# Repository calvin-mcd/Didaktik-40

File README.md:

# Didaktik 40

The Didaktik 40 is a retro-style keyboard taking its inspiration form the czech homecomputer, the [didaktik gama](https://en.wikipedia.org/wiki/Didaktik#Didaktik_Gama). While offering its original layout, it also supports more modern split and single spacebar bottomrow configurations as well as two rotary encoders.
The case is designed by gizzle13. It is a 2 degree, 2 piece case with top mounting for either simple or burger topmounting. It uses an old-school unified daughterboard for the usb port. The case and pcb furthermore support 2 leds, just like on the original case, and another hole to access the reset button.

## Layout

[Link](http://www.keyboard-layout-editor.com/#/gists/80f2dfd555ef09043852ad12f22f6b8f)

## Firmware

The basic firmware is set up to use the leds as layer indicators. Top for layer 1, bottom for layer 2, both for layer 3. There is hardware support for a speaker and for rgb strip but this is not enabled by default due to firmware size. Also note that the audio and rgb haven't been fully tested yet.

## Case

The case is designed by gizzle13. Case files can be found in the respective folder. It is designed to use m2 heatinserts. 

If you are in the EU consider asking gizzle to print the case for you to support them!

## Disclaimer

This PCB has been fully tested and confirmed to work. The members of the PCB development team are however not liable if you end up with a non-functional pcb. Order at your own risk. Support will not be provided but pull requests will be reviewed and possibly accepted.

## License

This project is released under the GPL v3 License. Please refer to the LICENCE file.

## Credits

big thanks to gizzle13 for making this project possible. The whole idea really lives and thrives with the case!

As always big thanks also to the many people who inspired and helped with this board!

Any questions, contact Calvin0563 on Discord.

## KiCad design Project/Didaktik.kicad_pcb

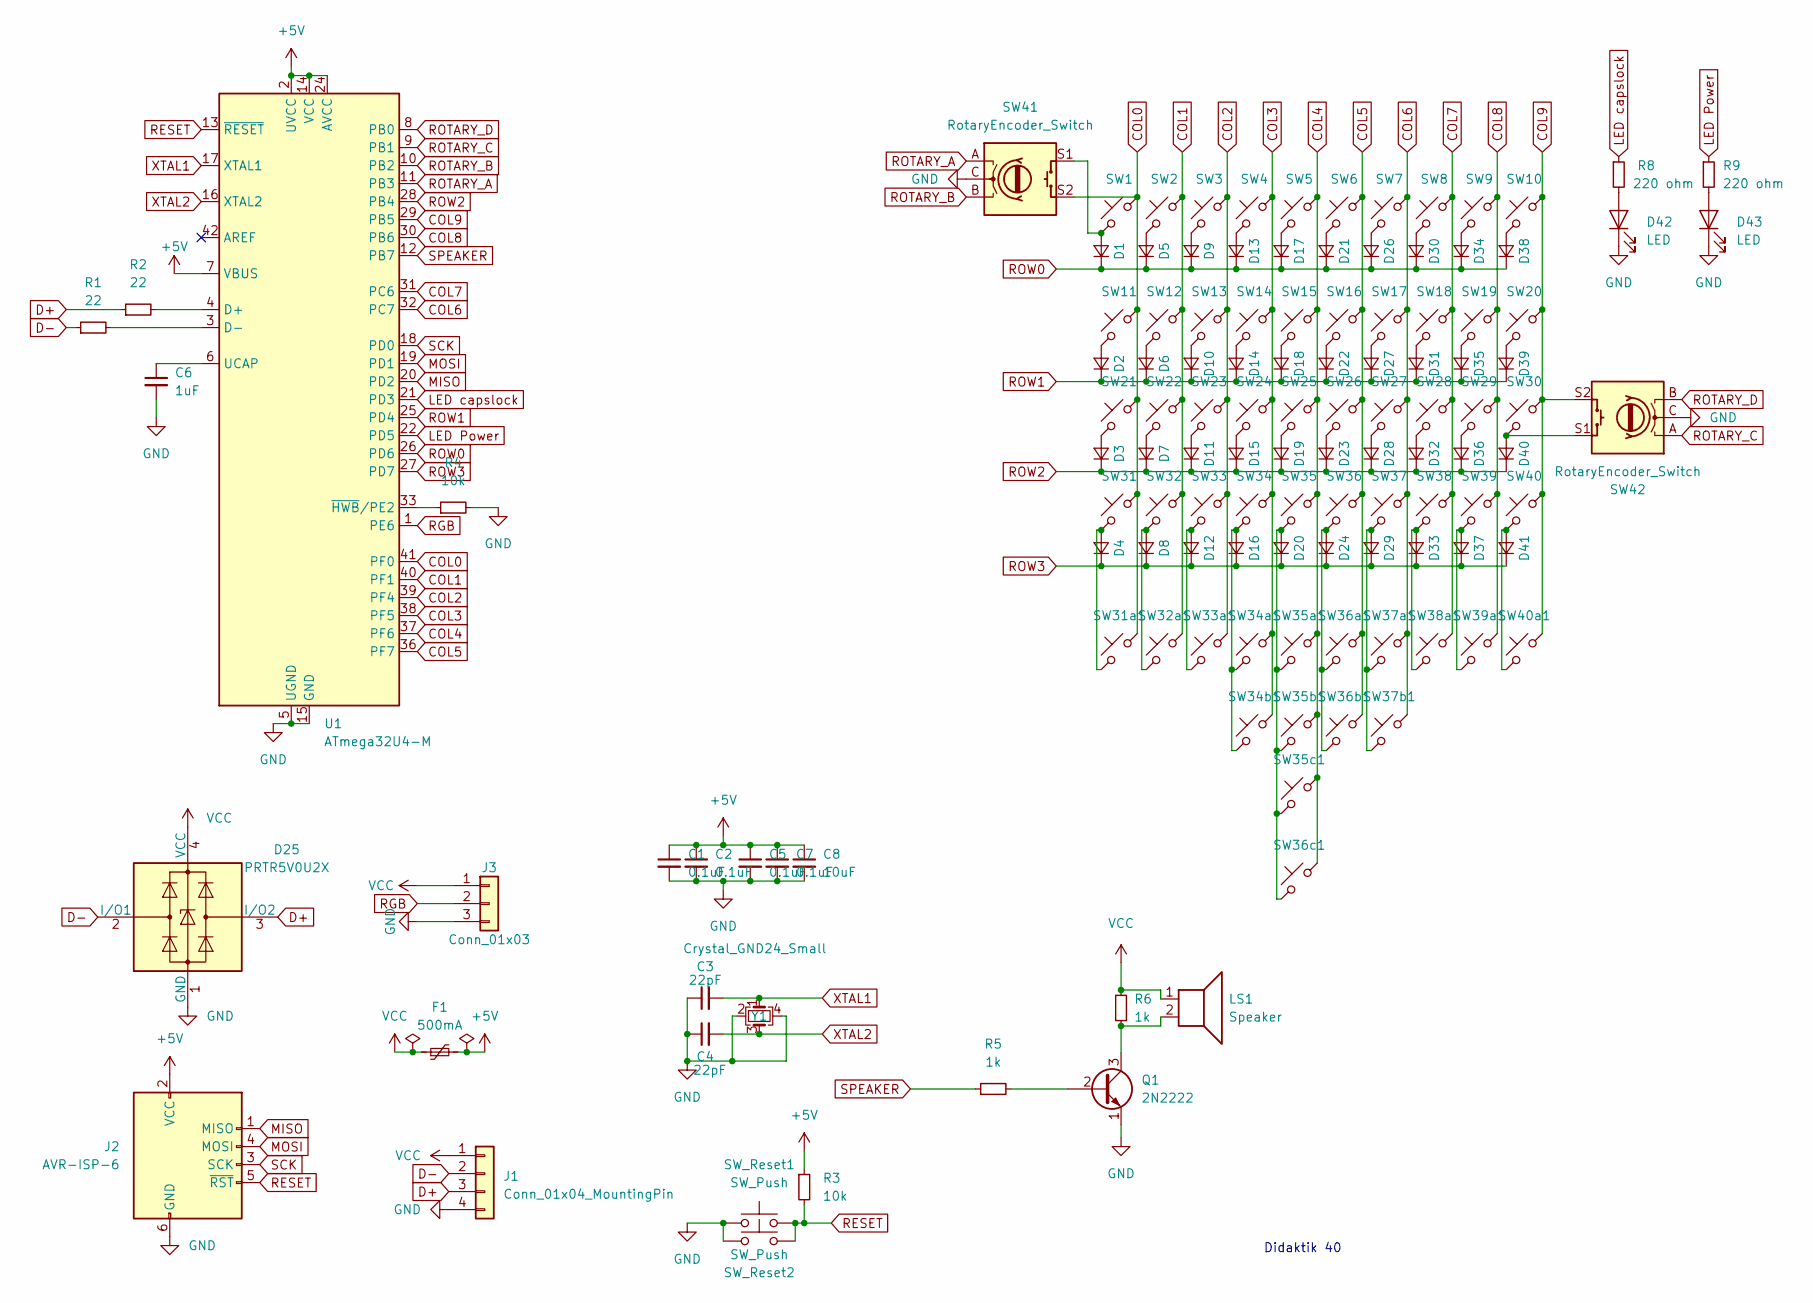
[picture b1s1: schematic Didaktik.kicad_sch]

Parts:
C1, C2, C5, C7: 0.1uF; C_0402_1005Metric
C3, C4: 22pF; C_0402_1005Metric
C6: 1uF; C_0402_1005Metric
C8: 10uF; C_0402_1005Metric
D1, D2, D3, D4, D5, D6, D7, D8, D9, D10, D11, D12, D13, D14, D15, D16, D17, D18, D19, D20, D21, D22, D23, D24, D26, D27, D28, D29, D30, D31, D32, D33, D34, D35, D36, D37, D38, D39, D40, D41: D_Small; D_SOD-123F
D25: PRTR5V0U2X; SOT-143
D42, D43: LED; LED_3mm
F1: 500mA; Fuse_1206_3216Metric
J1: Conn_01x04_MountingPin; JST-SR-4
J2: AVR-ISP-6; Reset_Pretty-Mask
J3: Conn_01x03; PinSocket_1x03_P2.00mm_Vertical
LS1: Speaker; AST1109MLTRQ
Q1: 2N2222; SOT-23
R1, R2: 22; R_0402_1005Metric
R3, R4: 10k; R_0402_1005Metric
R5: 1k; Diode-Hybrid-Back
R6: 1k; R_0402_1005Metric
R8, R9: 220 ohm; R_0402_1005Metric
SW1, SW2, SW3, SW4, SW5, SW6, SW7, SW8, SW9, SW10, SW11, SW12, SW13, SW14, SW15, SW16, SW17, SW18, SW19, SW20, SW21, SW22, SW23, SW24, SW25, SW26, SW27, SW28, SW29, SW30, SW31a1, SW32, SW32a1, SW33, SW33a1, SW34, SW34a1, SW35, SW36, SW37, SW37a1, SW38, SW38a1, SW39, SW39a1, SW40a1: SW_Push_45deg; MXOnly-1U-NoLED
SW31, SW35a1, SW36a1, SW40: SW_Push_45deg; MXOnly-1.5U-NoLED
SW34b1, SW37b1: SW_Push_45deg; MXOnly-3U-ReversedStabilizers-NoLED
SW35b1, SW36b1: SW_Push_45deg; MXOnly-2U-ReversedStabilizers-NoLED
SW35c1: SW_Push_45deg; MXOnly-6U-Centered-ReversedStabilizers-NoLED
SW36c1: SW_Push_45deg; MXOnly-7U-ReversedStabilizers-NoLED
SW41, SW42: RotaryEncoder_Switch; RotaryEncoder_EC11-no-legs
SW_Reset1: SW_Push; SKQG-1155865
SW_Reset2: SW_Push; PinHeader_1x02_P2.54mm_Vertical
U1: ATmega32U4-M; QFN-44-1EP_7x7mm_P0.5mm_EP5.2x5.2mm
Y1: Crystal_GND24_Small; Crystal_SMD_3225-4Pin_3.2x2.5mm

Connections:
+5V: C1.1, C2.1, C5.1, C7.1, C8.1, F1.2, J2.2 (VCC), R3.1, U1.2 (UVCC), U1.7 (VBUS), U1.14 (VCC), U1.24 (AVCC), U1.34 (VCC), U1.44 (AVCC)
COL0: SW1.1, SW11.1, SW21.1, SW31.1, SW31a1.1, SW41.S2, U1.41 (PF0)
COL1: SW2.1, SW12.1, SW22.1, SW32.1, SW32a1.1, U1.40 (PF1)
COL2: SW3.1, SW13.1, SW23.1, SW33.1, SW33a1.1, U1.39 (PF4)
COL3: SW4.1, SW14.1, SW24.1, SW34.1, SW34a1.1, SW34b1.1, U1.38 (PF5)
COL4: SW5.1, SW15.1, SW25.1, SW35.1, SW35a1.1, SW35b1.1, SW35c1.1, SW36c1.1, U1.37 (PF6)
COL5: SW6.1, SW16.1, SW26.1, SW36.1, SW36a1.1, SW36b1.1, U1.36 (PF7)
COL6: SW7.1, SW17.1, SW27.1, SW37.1, SW37a1.1, SW37b1.1, U1.32 (PC7)
COL7: SW8.1, SW18.1, SW28.1, SW38.1, SW38a1.1, U1.31 (PC6)
COL8: SW9.1, SW19.1, SW29.1, SW39.1, SW39a1.1, U1.30 (PB6)
COL9: SW10.1, SW20.1, SW30.1, SW40.1, SW40a1.1, SW42.S2, U1.29 (PB5)
D+: D25.3 (I/O2), J1.3, R2.1
D-: D25.2 (I/O1), J1.2, R1.1
GND: C1.2, C2.2, C3.1, C4.1, C5.2, C6.2, C7.2, C8.2, D25.1 (GND), D42.1 (K), D43.1 (K), J1.4, J2.6 (GND), J3.3, Q1.1 (E), R4.2, SW41.C, SW42.C, SW_Reset1.1, SW_Reset2.1, U1.5 (UGND), U1.15 (GND), U1.23 (GND), U1.35 (GND), U1.43 (GND), U1.45 (GND), Y1.2, Y1.4
LED Power: R9.1, U1.22 (PD5)
LED capslock: R8.1, U1.21 (PD3)
MISO: J2.1 (MISO), U1.20 (PD2)
MOSI: J2.4 (MOSI), U1.19 (PD1)
unnamed: D1.2 (A), SW1.2, SW41.S1
unnamed: D2.2 (A), SW11.2
unnamed: D3.2 (A), SW21.2
unnamed: D4.2 (A), SW31.2, SW31a1.2
unnamed: D5.2 (A), SW2.2
unnamed: D6.2 (A), SW12.2
unnamed: D7.2 (A), SW22.2
unnamed: D8.2 (A), SW32.2, SW32a1.2
unnamed: D9.2 (A), SW3.2
unnamed: D10.2 (A), SW13.2
unnamed: D11.2 (A), SW23.2
unnamed: D12.2 (A), SW33.2, SW33a1.2
unnamed: D13.2 (A), SW4.2
unnamed: D14.2 (A), SW14.2
unnamed: D15.2 (A), SW24.2
unnamed: D16.2 (A), SW34.2, SW34a1.2, SW34b1.2
unnamed: D17.2 (A), SW5.2
unnamed: D18.2 (A), SW15.2
unnamed: D19.2 (A), SW25.2
unnamed: D20.2 (A), SW35.2, SW35a1.2, SW35b1.2, SW35c1.2, SW36c1.2
unnamed: D21.2 (A), SW6.2
unnamed: D22.2 (A), SW16.2
unnamed: D23.2 (A), SW26.2
unnamed: D24.2 (A), SW36.2, SW36a1.2, SW36b1.2
unnamed: D26.2 (A), SW7.2
unnamed: D27.2 (A), SW17.2
unnamed: D28.2 (A), SW27.2
unnamed: D29.2 (A), SW37.2, SW37a1.2, SW37b1.2
unnamed: D30.2 (A), SW8.2
unnamed: D31.2 (A), SW18.2
unnamed: D32.2 (A), SW28.2
unnamed: D33.2 (A), SW38.2, SW38a1.2
unnamed: D34.2 (A), SW9.2
unnamed: D35.2 (A), SW19.2
unnamed: D36.2 (A), SW29.2
unnamed: D37.2 (A), SW39.2, SW39a1.2
unnamed: D38.2 (A), SW10.2
unnamed: D39.2 (A), SW20.2
unnamed: D40.2 (A), SW30.2, SW42.S1
unnamed: D41.2 (A), SW40.2, SW40a1.2
unnamed: D42.2 (A), R8.2
unnamed: D43.2 (A), R9.2
unnamed: Q1.2 (B), R5.2
unnamed: LS1.2, Q1.3 (C), R6.2
unnamed: R2.2, U1.4 (D+)
unnamed: R1.2, U1.3 (D-)
unnamed: C6.1, U1.6 (UCAP)
unnamed: R4.1, U1.33 (~HWB/PE2)
RESET: J2.5 (~RST), R3.2, SW_Reset1.2, SW_Reset2.2, U1.13 (~RESET)
RGB: J3.2, U1.1 (PE6)
ROTARY_A: SW41.A, U1.11 (PB3)
ROTARY_B: SW41.B, U1.10 (PB2)
ROTARY_C: SW42.A, U1.9 (PB1)
ROTARY_D: SW42.B, U1.8 (PB0)
ROW0: D1.1 (K), D5.1 (K), D9.1 (K), D13.1 (K), D17.1 (K), D21.1 (K), D26.1 (K), D30.1 (K), D34.1 (K), D38.1 (K), U1.26 (PD6)
ROW1: D2.1 (K), D6.1 (K), D10.1 (K), D14.1 (K), D18.1 (K), D22.1 (K), D27.1 (K), D31.1 (K), D35.1 (K), D39.1 (K), U1.25 (PD4)
ROW2: D3.1 (K), D7.1 (K), D11.1 (K), D15.1 (K), D19.1 (K), D23.1 (K), D28.1 (K), D32.1 (K), D36.1 (K), D40.1 (K), U1.28 (PB4)
ROW3: D4.1 (K), D8.1 (K), D12.1 (K), D16.1 (K), D20.1 (K), D24.1 (K), D29.1 (K), D33.1 (K), D37.1 (K), D41.1 (K), U1.27 (PD7)
SCK: J2.3 (SCK), U1.18 (PD0)
SPEAKER: R5.1, U1.12 (PB7)
VCC: D25.4 (VCC), F1.1, J1.1, J3.1, LS1.1, R6.1
XTAL1: C3.2, U1.17 (XTAL1), Y1.1
XTAL2: C4.2, U1.16 (XTAL2), Y1.3

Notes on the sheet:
Didaktik 40

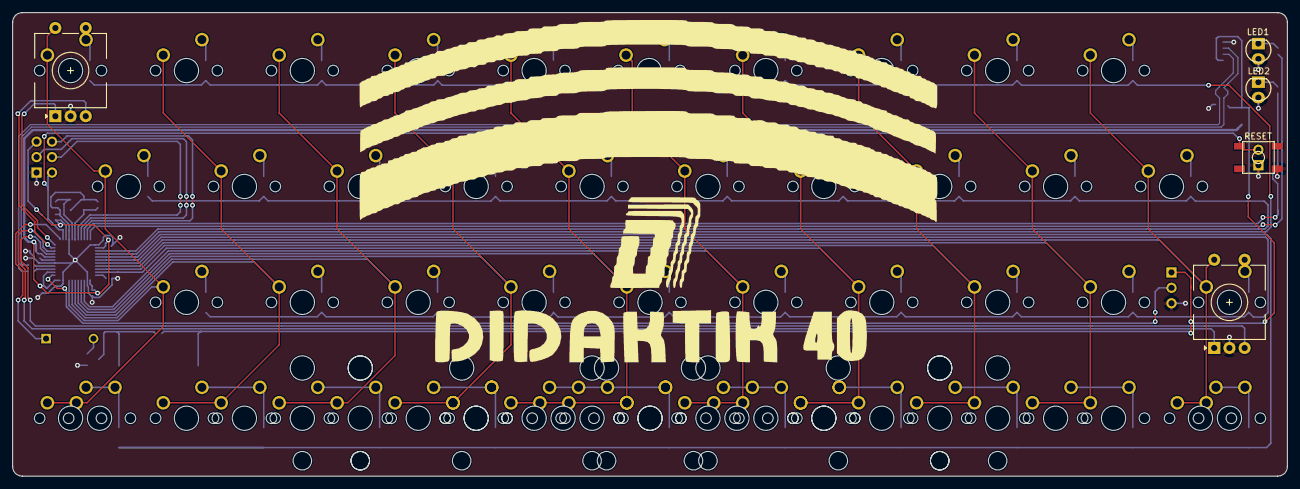
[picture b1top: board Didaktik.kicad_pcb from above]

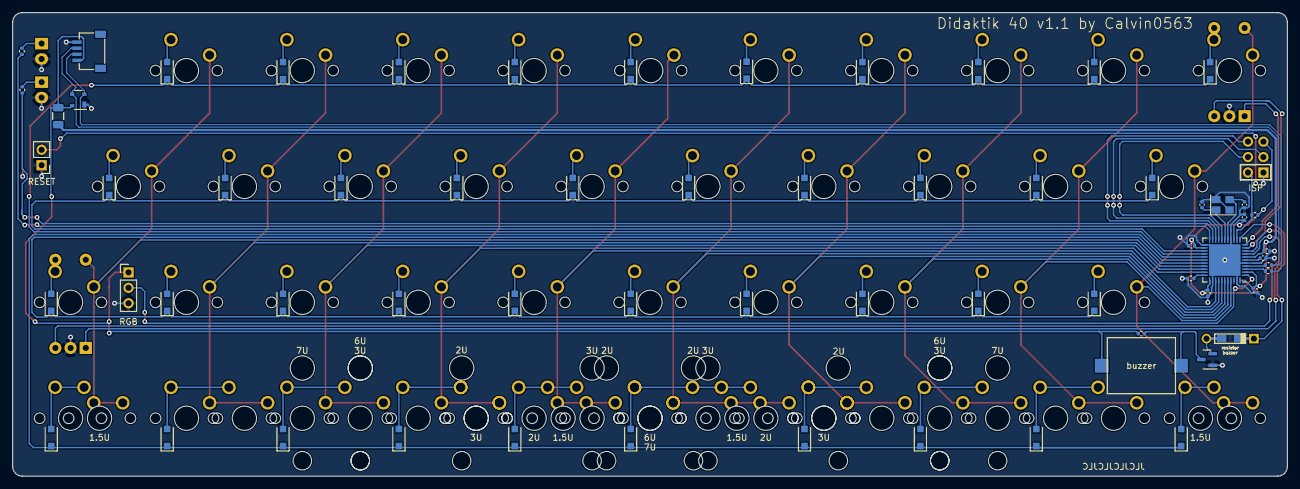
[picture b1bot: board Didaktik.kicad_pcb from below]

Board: 2 copper layers, 209.6 x 76.2 mm, 127 parts (65 on the bottom side), 81 nets.

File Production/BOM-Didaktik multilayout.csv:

Id,Designator,Package,Quantity,Designation,Supplier and ref
1,"D29,D6,D14,D40,D8,D3,D36,D32,D1,D15,D34,D23,D21,D39,D30,D41,D20,D24,D26,D22,D13,D7,D4,D38,D31,D2,D9,D12,D35,D33,D17,D27,D16,D28,D18,D5,D19,D10,D37,D11",D_SOD-123,40,D_Small,C64898
2,"C1,C5,C7,C2",C_0402_1005Metric,4,0.1uF,C161338
3,"C4,C3",C_0402_1005Metric,2,22pF,C106203
4,"R4,R3",R_0402_1005Metric,2,10k,C77131
5,Y1,Crystal_SMD_3225-4Pin_3.2x2.5mm,1,Crystal_GND24_Small,C133336
6,U1,QFN-44-1EP_7x7mm_P0.5mm_EP5.2x5.2mm,1,ATmega32U4-M,C112161
7,Q1,SOT-23,1,2N2222,C2150
8,F1,Fuse_1206_3216Metric,1,500mA,C155093
9,R6,R_0402_1005Metric,1,1k,C11702
10,J1,JST-SR-4,1,Conn_01x04_MountingPin,C160404
11,"R2,R1",R_0402_1005Metric,2,22,C25092
12,"R9,R8",R_0402_1005Metric,2,220 ohm,C316269
13,D25,SOT-143,1,PRTR5V0U2X,C2827688
14,C6,C_0402_1005Metric,1,1uF,C182246
15,C8,C_0402_1005Metric,1,10uF,C237279

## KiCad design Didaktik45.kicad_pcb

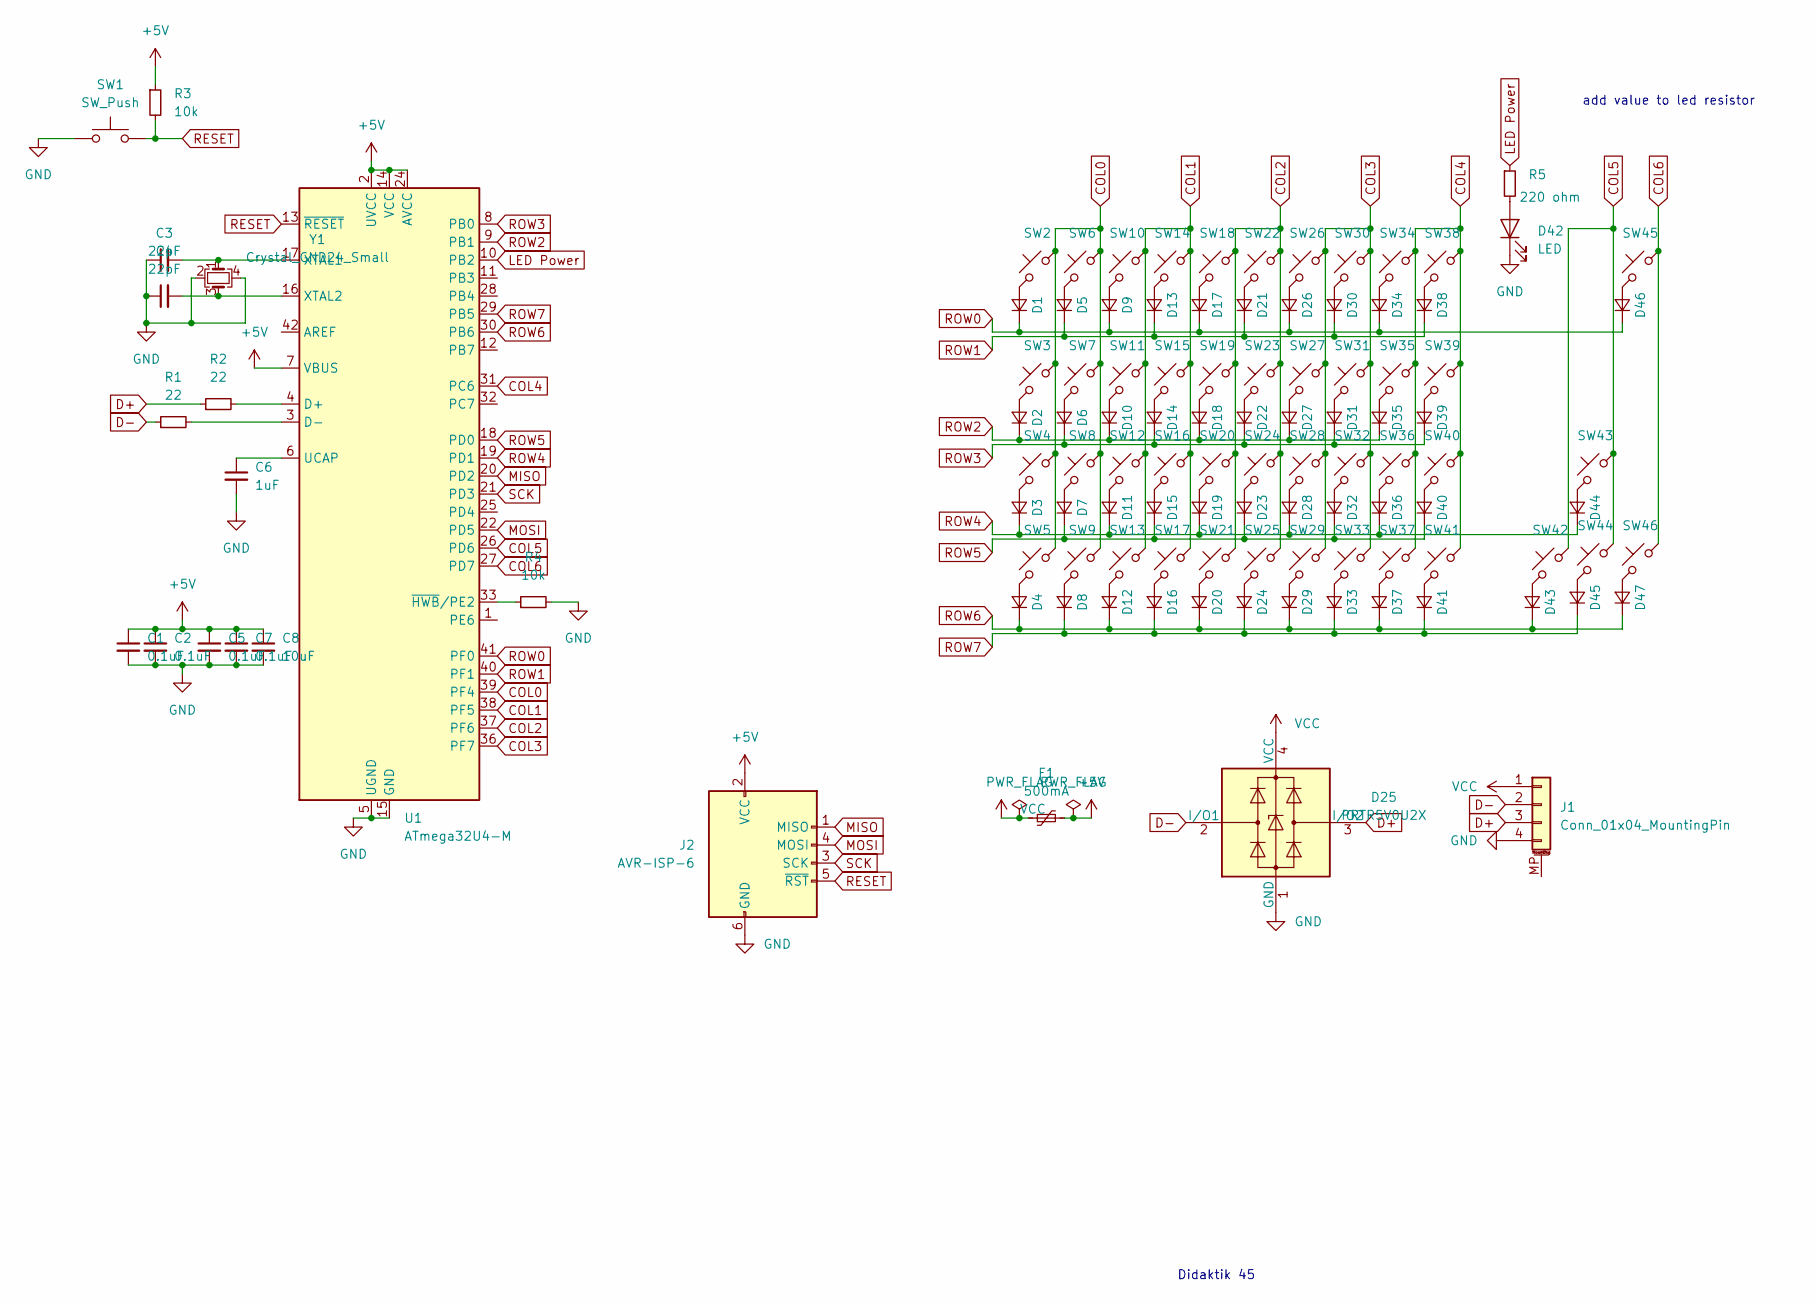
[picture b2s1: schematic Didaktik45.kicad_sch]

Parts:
C1, C2, C5, C7: 0.1uF; C_0402_1005Metric
C3, C4: 22pF; C_0402_1005Metric
C6: 1uF; C_0402_1005Metric
C8: 10uF; C_0402_1005Metric
D1, D2, D3, D4, D5, D6, D7, D8, D9, D10, D11, D12, D13, D14, D15, D16, D17, D18, D19, D20, D21, D22, D23, D24, D26, D27, D28, D29, D30, D31, D32, D33, D34, D35, D36, D37, D38, D39, D40, D41, D43, D44, D45, D46, D47: D_Small; D_SOD-123
D25: PRTR5V0U2X; SOT-143
D42: LED; LED_3mm
F1: 500mA; Fuse_1206_3216Metric
J1: Conn_01x04_MountingPin; JST-SR-4
J2: AVR-ISP-6; Reset_Pretty-Mask
R1, R2: 22; R_0402_1005Metric
R3, R4: 10k; R_0402_1005Metric
R5: 220 ohm; R_0402_1005Metric
SW1: SW_Push; SKQG-1155865
SW2, SW3, SW4, SW5, SW6, SW7, SW8, SW9, SW10, SW11, SW12, SW13, SW14, SW15, SW16, SW17, SW18, SW19, SW20, SW21, SW22, SW23, SW24, SW25, SW26, SW27, SW28, SW29, SW30, SW31, SW32, SW33, SW34, SW35, SW36, SW37, SW38, SW39, SW40, SW41, SW42, SW43, SW44, SW45, SW46: SW_Push_45deg; MX-Alps-Choc-1U-NoLED
U1: ATmega32U4-M; QFN-44-1EP_7x7mm_P0.5mm_EP5.2x5.2mm
Y1: Crystal_GND24_Small; Crystal_SMD_3225-4Pin_3.2x2.5mm

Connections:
+5V: C1.1, C2.1, C5.1, C7.1, C8.1, F1.2, J2.2 (VCC), R3.1, U1.2 (UVCC), U1.7 (VBUS), U1.14 (VCC), U1.24 (AVCC), U1.34 (VCC), U1.44 (AVCC)
COL0: SW2.1, SW3.1, SW4.1, SW5.1, SW6.1, SW7.1, SW8.1, SW9.1, U1.39 (PF4)
COL1: SW10.1, SW11.1, SW12.1, SW13.1, SW14.1, SW15.1, SW16.1, SW17.1, U1.38 (PF5)
COL2: SW18.1, SW19.1, SW20.1, SW21.1, SW22.1, SW23.1, SW24.1, SW25.1, U1.37 (PF6)
COL3: SW26.1, SW27.1, SW28.1, SW29.1, SW30.1, SW31.1, SW32.1, SW33.1, U1.36 (PF7)
COL4: SW34.1, SW35.1, SW36.1, SW37.1, SW38.1, SW39.1, SW40.1, SW41.1, U1.31 (PC6)
COL5: SW42.1, SW43.1, SW44.1, U1.26 (PD6)
COL6: SW45.1, SW46.1, U1.27 (PD7)
D+: D25.3 (I/O2), J1.3, R2.1
D-: D25.2 (I/O1), J1.2, R1.1
GND: C1.2, C2.2, C3.1, C4.1, C5.2, C6.2, C7.2, C8.2, D25.1 (GND), D42.1 (K), J1.4, J2.6 (GND), R4.2, SW1.1, U1.5 (UGND), U1.15 (GND), U1.23 (GND), U1.35 (GND), U1.43 (GND), U1.45 (GND), Y1.2, Y1.4
LED Power: R5.1, U1.10 (PB2)
MISO: J2.1 (MISO), U1.20 (PD2)
MOSI: J2.4 (MOSI), U1.22 (PD5)
unnamed: C3.2, U1.17 (XTAL1), Y1.1
unnamed: C4.2, U1.16 (XTAL2), Y1.3
unnamed: C6.1, U1.6 (UCAP)
unnamed: D1.2 (A), SW2.2
unnamed: D2.2 (A), SW3.2
unnamed: D3.2 (A), SW4.2
unnamed: D4.2 (A), SW5.2
unnamed: D5.2 (A), SW6.2
unnamed: D6.2 (A), SW7.2
unnamed: D7.2 (A), SW8.2
unnamed: D8.2 (A), SW9.2
unnamed: D9.2 (A), SW10.2
unnamed: D10.2 (A), SW11.2
unnamed: D11.2 (A), SW12.2
unnamed: D12.2 (A), SW13.2
unnamed: D13.2 (A), SW14.2
unnamed: D14.2 (A), SW15.2
unnamed: D15.2 (A), SW16.2
unnamed: D16.2 (A), SW17.2
unnamed: D17.2 (A), SW18.2
unnamed: D18.2 (A), SW19.2
unnamed: D19.2 (A), SW20.2
unnamed: D20.2 (A), SW21.2
unnamed: D21.2 (A), SW22.2
unnamed: D22.2 (A), SW23.2
unnamed: D23.2 (A), SW24.2
unnamed: D24.2 (A), SW25.2
unnamed: D26.2 (A), SW26.2
unnamed: D27.2 (A), SW27.2
unnamed: D28.2 (A), SW28.2
unnamed: D29.2 (A), SW29.2
unnamed: D30.2 (A), SW30.2
unnamed: D31.2 (A), SW31.2
unnamed: D32.2 (A), SW32.2
unnamed: D33.2 (A), SW33.2
unnamed: D34.2 (A), SW34.2
unnamed: D35.2 (A), SW35.2
unnamed: D36.2 (A), SW36.2
unnamed: D37.2 (A), SW37.2
unnamed: D38.2 (A), SW38.2
unnamed: D39.2 (A), SW39.2
unnamed: D40.2 (A), SW40.2
unnamed: D41.2 (A), SW41.2
unnamed: D42.2 (A), R5.2
unnamed: D43.2 (A), SW42.2
unnamed: D44.2 (A), SW43.2
unnamed: D45.2 (A), SW44.2
unnamed: D46.2 (A), SW45.2
unnamed: D47.2 (A), SW46.2
unnamed: R1.2, U1.3 (D-)
unnamed: R2.2, U1.4 (D+)
unnamed: R4.1, U1.33 (~HWB/PE2)
RESET: J2.5 (~RST), R3.2, SW1.2, U1.13 (~RESET)
ROW0: D1.1 (K), D9.1 (K), D17.1 (K), D26.1 (K), D34.1 (K), D46.1 (K), U1.41 (PF0)
ROW1: D5.1 (K), D13.1 (K), D21.1 (K), D30.1 (K), D38.1 (K), U1.40 (PF1)
ROW2: D2.1 (K), D10.1 (K), D18.1 (K), D27.1 (K), D35.1 (K), U1.9 (PB1)
ROW3: D6.1 (K), D14.1 (K), D22.1 (K), D31.1 (K), D39.1 (K), U1.8 (PB0)
ROW4: D3.1 (K), D11.1 (K), D19.1 (K), D28.1 (K), D36.1 (K), D44.1 (K), U1.19 (PD1)
ROW5: D7.1 (K), D15.1 (K), D23.1 (K), D32.1 (K), D40.1 (K), U1.18 (PD0)
ROW6: D4.1 (K), D12.1 (K), D20.1 (K), D29.1 (K), D37.1 (K), D43.1 (K), D47.1 (K), U1.30 (PB6)
ROW7: D8.1 (K), D16.1 (K), D24.1 (K), D33.1 (K), D41.1 (K), D45.1 (K), U1.29 (PB5)
SCK: J2.3 (SCK), U1.21 (PD3)
VCC: D25.4 (VCC), F1.1, J1.1

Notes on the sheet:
Didaktik 45
add value to led resistor

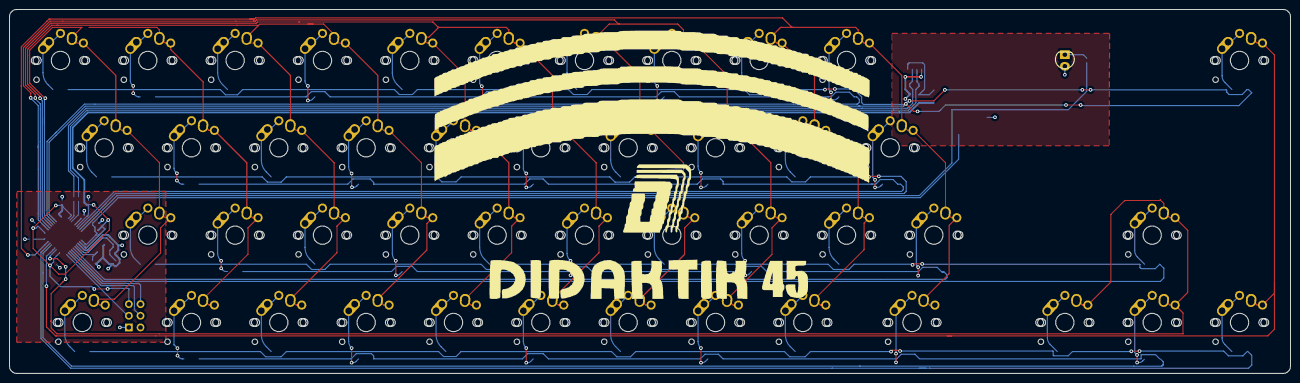
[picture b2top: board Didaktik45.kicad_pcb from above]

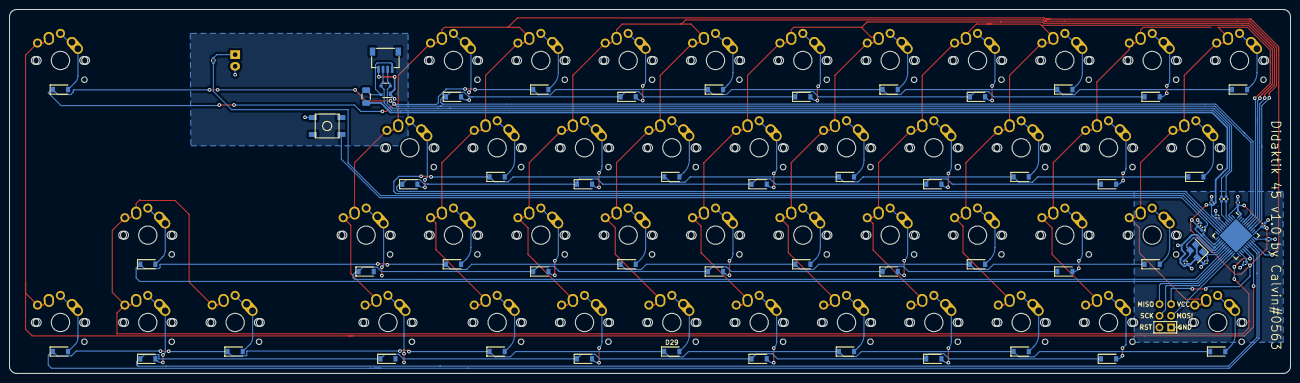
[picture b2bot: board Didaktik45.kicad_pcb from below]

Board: 2 copper layers, 279.4 x 79.4 mm, 111 parts (65 on the bottom side), 77 nets.

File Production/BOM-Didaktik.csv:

Comment,Designator,Footprint,LCSC
22pF,"C3,C4",C_0402_1005Metric,C106203
ATmega32U4-M,U1,QFN-44-1EP_7x7mm_P0.5mm_EP5.2x5.2mm,C112161
1k,R6,R_0402_1005Metric,C11702
Crystal_GND24_Small,Y1,Crystal_SMD_3225-4Pin_3.2x2.5mm,C133336
0.1uF,"C1,C2,C5,C7",C_0402_1005Metric,C1525
Conn_01x04_MountingPin,J1,JST-SR-4,C160404
1uF,C6,C_0402_1005Metric,C182246
2N2222,Q1,SOT-23,C2150
10uF,C8,C_0402_1005Metric,C237279
22,"R1,R2",R_0402_1005Metric,C25092
PRTR5V0U2X,D25,SOT-143,C2827688
10k,"R3,R4",R_0402_1005Metric,C3015825
220 ohm,"R8,R9",R_0402_1005Metric,C316269
D_Small,"D1,D10,D11,D12,D13,D14,D15,D16,D17,D18,D19,D2,D20,D21,D22,D23,D24,D26,D27,D28,D29,D3,D30,D31,D32,D33,D34,D35,D36,D37,D38,D39,D4,D40,D41,D5,D6,D7,D8,D9",D_SOD-123F,C64898
500mA,F1,Fuse_1206_3216Metric,C70076
SW_Push_45deg,SW33,MXOnly-1U-NoLED,
SW_Push_45deg,SW15,MXOnly-1U-NoLED,
SW_Push_45deg,SW36c1,MXOnly-7U-ReversedStabilizers-NoLED,
SW_Push_45deg,SW7,MXOnly-1U-NoLED,
SW_Push_45deg,SW27,MXOnly-1U-NoLED,
SW_Push_45deg,SW34b1,MXOnly-3U-ReversedStabilizers-NoLED,
SW_Push_45deg,SW14,MXOnly-1U-NoLED,
SW_Push_45deg,SW33a1,MXOnly-1U-NoLED,
SW_Push_45deg,SW9,MXOnly-1U-NoLED,
LED,D42,LED_3mm,
SW_Push_45deg,SW29,MXOnly-1U-NoLED,
SW_Push_45deg,SW8,MXOnly-1U-NoLED,
SW_Push_45deg,SW35b1,MXOnly-2U-ReversedStabilizers-NoLED,
SW_Push_45deg,SW2,MXOnly-1U-NoLED,
SW_Push_45deg,SW34,MXOnly-1U-NoLED,
SW_Push_45deg,SW24,MXOnly-1U-NoLED,
SW_Push_45deg,SW31,MXOnly-1.5U-NoLED,
SW_Push_45deg,SW37a1,MXOnly-1U-NoLED,
SW_Push_45deg,SW20,MXOnly-1U-NoLED,
SW_Push_45deg,SW5,MXOnly-1U-NoLED,
SW_Push_45deg,SW40a1,MXOnly-1U-NoLED,
SW_Push_45deg,SW35,MXOnly-1U-NoLED,
SW_Push_45deg,SW31a1,MXOnly-1U-NoLED,
SW_Push_45deg,SW38,MXOnly-1U-NoLED,
SW_Push_45deg,SW12,MXOnly-1U-NoLED,
SW_Push_45deg,SW22,MXOnly-1U-NoLED,
SW_Push_45deg,SW36a1,MXOnly-1.5U-NoLED,
SW_Push_45deg,SW36b1,MXOnly-2U-ReversedStabilizers-NoLED,
SW_Push_45deg,SW10,MXOnly-1U-NoLED,
SW_Push_45deg,SW35c1,MXOnly-6U-Centered-ReversedStabilizers-NoLED,
SW_Push_45deg,SW6,MXOnly-1U-NoLED,
SW_Push_45deg,SW19,MXOnly-1U-NoLED,
SW_Push_45deg,SW3,MXOnly-1U-NoLED,
SW_Push_45deg,SW17,MXOnly-1U-NoLED,
SW_Push_45deg,SW39,MXOnly-1U-NoLED,
SW_Push_45deg,SW11,MXOnly-1U-NoLED,
SW_Push_45deg,SW21,MXOnly-1U-NoLED,
SW_Push_45deg,SW16,MXOnly-1U-NoLED,
SW_Push_45deg,SW18,MXOnly-1U-NoLED,
RotaryEncoder_Switch,SW42,RotaryEncoder_EC11-no-legs,
SW_Push_45deg,SW32a1,MXOnly-1U-NoLED,
SW_Push_45deg,SW37b1,MXOnly-3U-ReversedStabilizers-NoLED,
SW_Push_45deg,SW34a1,MXOnly-1U-NoLED,
SW_Push_45deg,SW36,MXOnly-1U-NoLED,
SW_Push_45deg,SW28,MXOnly-1U-NoLED,
SW_Push_45deg,SW1,MXOnly-1U-NoLED,
SW_Push_45deg,SW40,MXOnly-1.5U-NoLED,
SW_Push_45deg,SW39a1,MXOnly-1U-NoLED,
SW_Push_45deg,SW37,MXOnly-1U-NoLED,
SW_Push_45deg,SW4,MXOnly-1U-NoLED,
SW_Push_45deg,SW35a1,MXOnly-1.5U-NoLED,
SW_Push_45deg,SW32,MXOnly-1U-NoLED,
SW_Push_45deg,SW26,MXOnly-1U-NoLED,
SW_Push_45deg,SW30,MXOnly-1U-NoLED,
SW_Push_45deg,SW38a1,MXOnly-1U-NoLED,
SW_Push_45deg,SW13,MXOnly-1U-NoLED,
RotaryEncoder_Switch,SW41,RotaryEncoder_EC11-no-legs,
SW_Push_45deg,SW25,MXOnly-1U-NoLED,
SW_Push_45deg,SW23,MXOnly-1U-NoLED,
Conn_01x03,J3,PinSocket_1x03_P2.00mm_Vertical,
Speaker,LS1,AST1109MLTRQ,
1k,R5,Diode-Hybrid-Back,
LED,D43,LED_3mm,
SW_Push,SW_Reset1,SKQG-1155865,
AVR-ISP-6,J2,Reset_Pretty-Mask,

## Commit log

2022-10-15 initial commit
    setting up libraries
2022-10-19 backup update
2022-10-20 switch placement done, basic matrix routing done
2022-10-20 added jts, started to arrange MCU components
2022-10-23 added leds
2022-10-23 cleaned schematics, continued routing
2022-10-23 all traces routed, schematics cleaned up
2022-10-23 full routing, silkscreens, zones
2022-10-23 created switchplate 40, cleaned 40s pcb. finished schematics for 45. created pcb project for 45
2022-10-23 D45 & D40 pcbs created & cleaned. D45 plate created
2022-10-24 added ISP to 40, added ISP schematics to 45
2022-10-25 cleaned up some traces, ran DRC
2022-10-25 slight alterations to routes
    changing rounded for sharp ones
2022-10-26 created small tap plate, exported all plates and pcb in step for case design
2022-10-26 moved step into its own folder
2022-10-30 added multi layout proto
2022-11-06 preparing files for prototyping
2022-11-10 updated routing, created footprints for bottom row
2022-11-10 cleaned routing, added multilayout to schematics and laid out footprints under the pcb
2022-11-12 added multi layout pcb, kept original
2022-11-12 routing multipcb
2022-11-12 set up multilayout
    need to check if all switches are really routed
    maybe get rid of 2U
2022-11-12 auto safe
2022-11-18 cleaning up the schematics / pcb for multi
2022-11-21 work on multi
2022-11-26 simplifying schematics, rerouting pcb
2022-11-26 save
2022-11-27 routing new simpler matrix on pcb
2022-11-28 some routing attemps
2022-12-10 small changes to multilayout
2022-12-11 pcb copy, footprint revision, rerouting needed
2022-12-11 redoing placement, first routing line tests
2022-12-11 revision multilayout
2022-12-11 reworking mcu placement and wiring
2022-12-12 full routing of mcu & matrix
2022-12-13 outlining case dimensions
2022-12-13 outlined case more, deliberating routing aesthetics
2022-12-14 cleaning up pcb & switch plate edge cut
2022-12-16 redoing JST placement, some routing, full boardGND fill
2022-12-17 clean up
2022-12-20 adding rotaries & rgb breakout
2022-12-22 added buzzer
2022-12-22 files
2022-12-22 created production files, pdfs for review
2022-12-24 production files
2022-12-27 cleaned up routing
    sudden 9th error isp ground via to gnd net?
2022-12-27 trying to export plate files
2023-01-02 edited buzzer schematics & pcb placement
2023-01-04 new production files
2023-01-04 cleaning up files
2023-01-04 auto save
2023-01-07 changed sod123 to sod123f
2023-01-08 rgb pin changed from 42 to 1, new production files
2023-01-10 license added
2023-01-11 backup
2023-01-12 backups
2023-01-22 cleaning up production files
2023-01-26 V1.1
    added double reset button, pinout
2023-01-26 V1.1 Reset Button finished
    cleaned project folder
2023-01-26 autosave
2023-02-13 cleanup
2023-02-18 clean up folders, created rp2040 version
2023-02-19 switch and matrix components placed
2023-02-19 MCU, component placement
2023-02-20 some more cleaner MCU component placement
    boot button aligned to plate cut
2023-04-13 MCU routing on rp2040 version
2023-05-29 updated BOM with correct parts
2023-06-30 added STEM project WIP
2023-09-12 added image of original didaktik gama
2023-09-24 small changes
2023-10-22 added STM project
2023-10-31 publish rep, update readme with fresh pictures
2024-02-12 added case files and updated the readme
